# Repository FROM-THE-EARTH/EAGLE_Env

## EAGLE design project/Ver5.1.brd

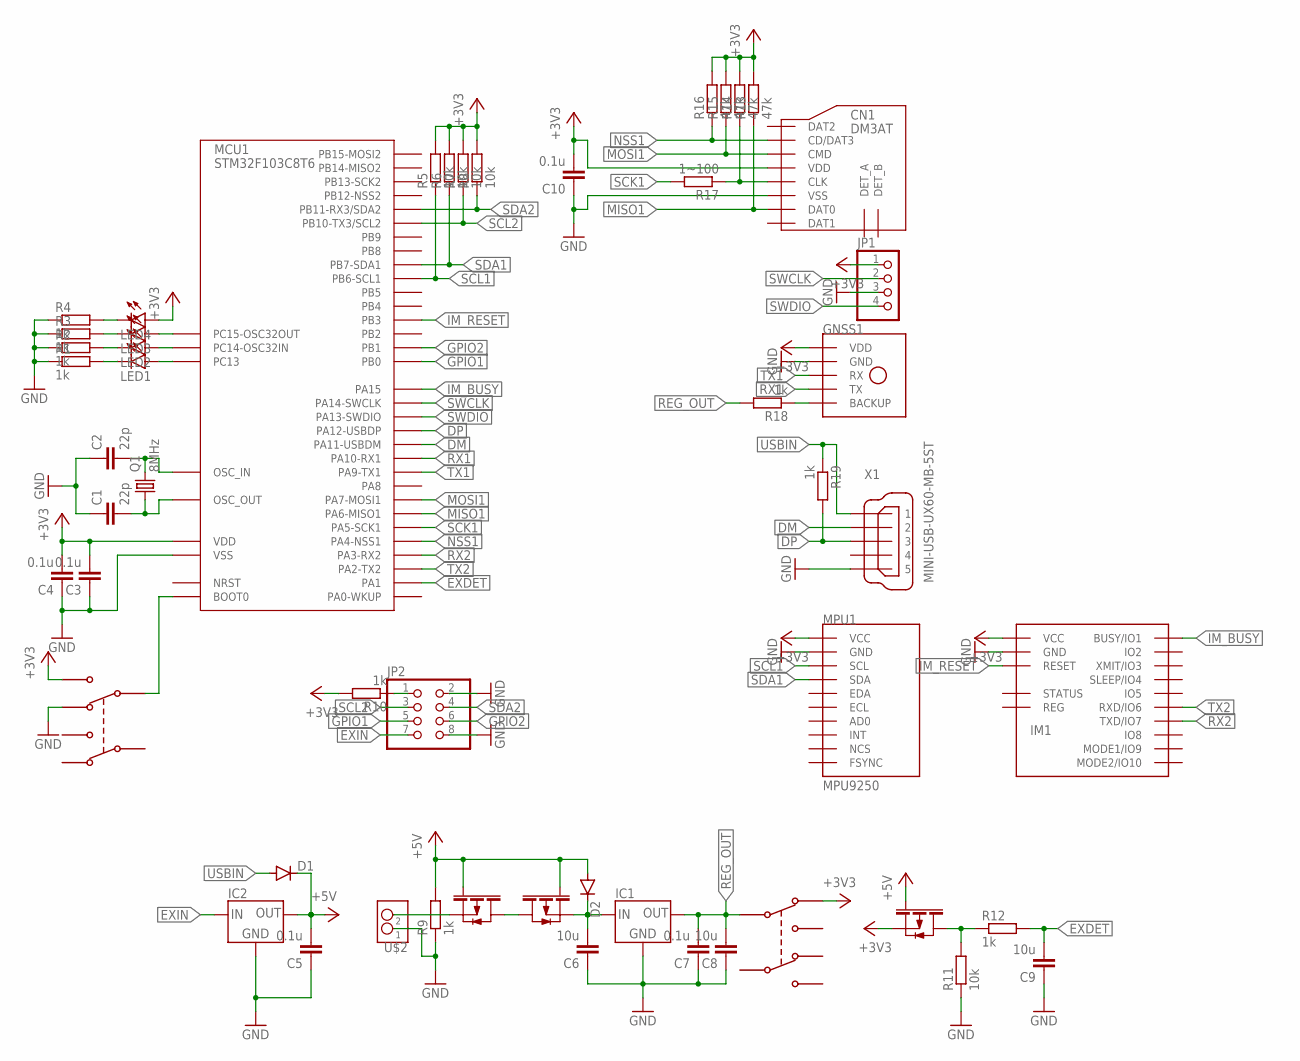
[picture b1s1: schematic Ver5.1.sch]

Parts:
C1, C2: 22p; C0805
C3, C4, C5, C7, C10: 0.1u; C0805
C6, C8, C9: 10u; C0805
CN1: DM3AT
D1, D2: DIODE-SOD123; SOD123
FET1, FET2, FET3: PCH; SOT-23
GNSS1: GYSFDMAXB
IC1: LT1117-3.3; SOT-223
IC2: LT1117-5; SOT-223
IM1: IM920C
JP1: PINHD-1X4/90; 1X04/90
JP2: PINHD-2X4; 2X04
LED1, LED2, LED3, LED4: LEDSML0805; SML0805
MCU1: STM32F103C8T6; LQFP48
MPU1: MPU9250; GY-9250
Q1: 8MHz; HC49/S
R1, R2, R3, R4, R9, R10, R12, R18, R19: 1k; R0805
R5, R6, R7, R8, R11: 10k; R0805
R13, R14, R15, R16: 47k; R0805
R17: 1~100; R0805
U$1, U$3: MSS22D18
U$2: S2B-XH-A
X1: MINI-USB-UX60-MB-5ST; UX60-MB-5ST

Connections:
+3V3: C3.2, C4.2, C10.2, CN1.VDD, FET3.P$2, GNSS1.P$16 (VDD), IM1.$P17 (VCC), JP1.1, LED4.A, MCU1.1 (VDD), MCU1.9 (VDD), MCU1.24 (VDD), MCU1.36 (VDD), MCU1.48 (VDD), MPU1.P1 (VCC), R5.2, R6.2, R7.2, R8.2, R10.2, R13.2, R14.2, R15.2, R16.2, U$1.P$0, U$3.P$3
+5V: C5.2, D1.C, D2.A, FET1.P$1, FET2.P$1, FET3.P$1, IC2.2 (OUT), R9.2
BOOT0: MCU1.44 (BOOT0), U$1.P$1
CLK_R: CN1.CLK, R14.1, R17.1
DM: MCU1.32 (PA11-USBDM), X1.2
DP: MCU1.33 (PA12-USBDP), R19.2, X1.3
EXDET: C9.2, MCU1.11 (PA1), R12.2
EXDET_R: FET3.P$3, R11.2, R12.1
EXIN: IC2.3 (IN), JP2.7
FET_FET: FET1.P$3, FET2.P$3
GND: C1.1, C2.1, C3.1, C4.1, C5.1, C6.1, C7.1, C8.1, C9.1, C10.1, CN1.VSS, GNSS1.P$1 (GND), GNSS1.P$2 (GND), GNSS1.P$7 (GND), GNSS1.P$10 (GND), GNSS1.P$12 (GND), GNSS1.P$19 (GND), GNSS1.P$20 (GND), IC1.4 (GND), IC2.4 (GND), IM1.$P18 (GND), JP1.3, JP2.2, JP2.8, MCU1.8 (VSS), MCU1.23 (VSS), MCU1.35 (VSS), MCU1.47 (VSS), MPU1.P2 (GND), R1.1, R2.1, R3.1, R4.1, R9.1, R11.1, U$1.P$2, U$2.P$1 (1), X1.5
GPIO1: JP2.5, MCU1.18 (PB0)
GPIO2: JP2.6, MCU1.19 (PB1)
GPS_BACKUP: GNSS1.P$14 (BACKUP), R18.1
IM_BUSY: IM1.$P1 (BUSY/IO1), MCU1.38 (PA15)
IM_RESET: IM1.$P19 (RESET), MCU1.39 (PB3)
LED1_R: LED1.C, R1.2
LED2_R: LED2.C, R2.2
LED3_R: LED3.C, R3.2
LED4_R: LED4.C, R4.2
LI_IN: FET1.P$2, U$2.P$2 (2)
MISO1: CN1.DAT0, MCU1.16 (PA6-MISO1), R13.1
MOSI1: CN1.CMD, MCU1.17 (PA7-MOSI1), R15.1
NSS1: CN1.CD/DAT3, MCU1.14 (PA4-NSS1), R16.1
OSC_IN: C2.2, MCU1.5 (OSC_IN), Q1.2
OSC_OUT: C1.2, MCU1.6 (OSC_OUT), Q1.1
PC13_LED: LED1.A, MCU1.2 (PC13)
PC14_LED: LED2.A, MCU1.3 (PC14-OSC32IN)
PC15_LED: LED3.A, MCU1.4 (PC15-OSC32OUT)
REG_IN: C6.2, D2.C, FET2.P$2, IC1.3 (IN)
REG_OUT: C7.2, C8.2, IC1.1 (OUT), IC1.2 (OUT), R18.2, U$3.P$4
RX1: GNSS1.P$5 (TX), MCU1.31 (PA10-RX1)
RX2: IM1.$P7 (TXD/IO7), MCU1.13 (PA3-RX2)
S3V3: JP2.1, R10.1
SCK1: MCU1.15 (PA5-SCK1), R17.2
SCL1: MCU1.42 (PB6-SCL1), MPU1.P3 (SCL), R5.1
SCL2: JP2.3, MCU1.21 (PB10-TX3/SCL2), R7.1
SDA1: MCU1.43 (PB7-SDA1), MPU1.P4 (SDA), R6.1
SDA2: JP2.4, MCU1.22 (PB11-RX3/SDA2), R8.1
SWCLK: JP1.2, MCU1.37 (PA14-SWCLK)
SWDIO: JP1.4, MCU1.34 (PA13-SWDIO)
TX1: GNSS1.P$3 (RX), MCU1.30 (PA9-TX1)
TX2: IM1.$P6 (RXD/IO6), MCU1.12 (PA2-TX2)
USBIN: D1.A, R19.1, X1.1

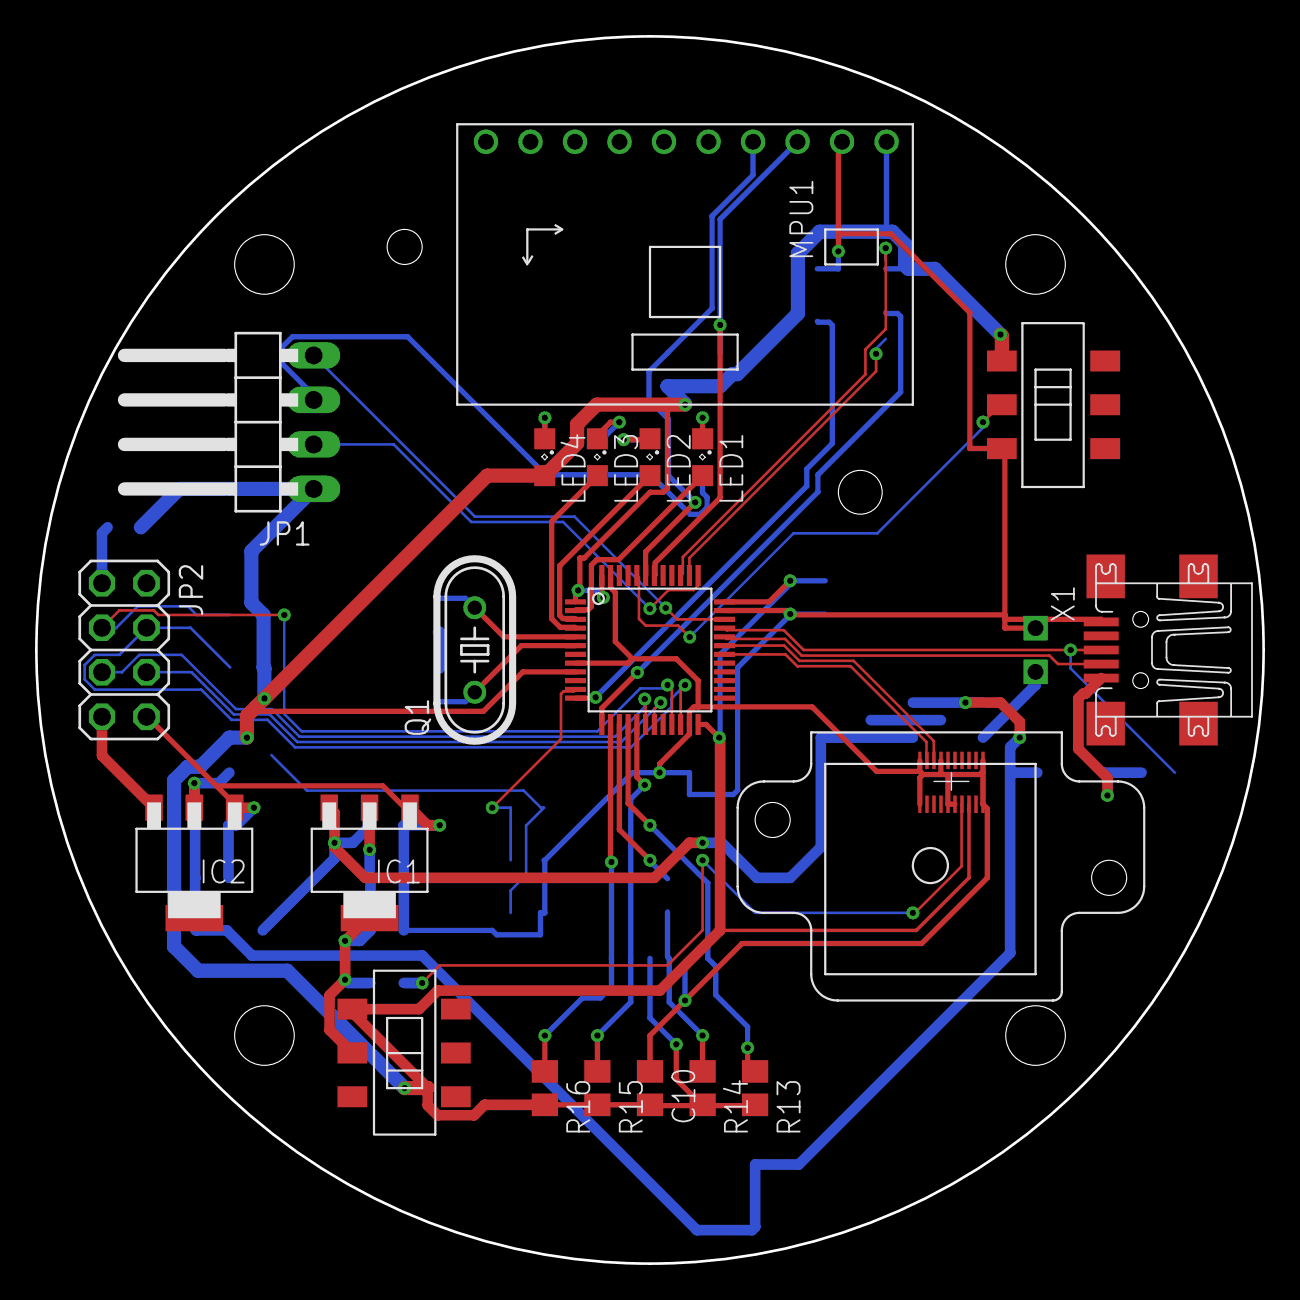
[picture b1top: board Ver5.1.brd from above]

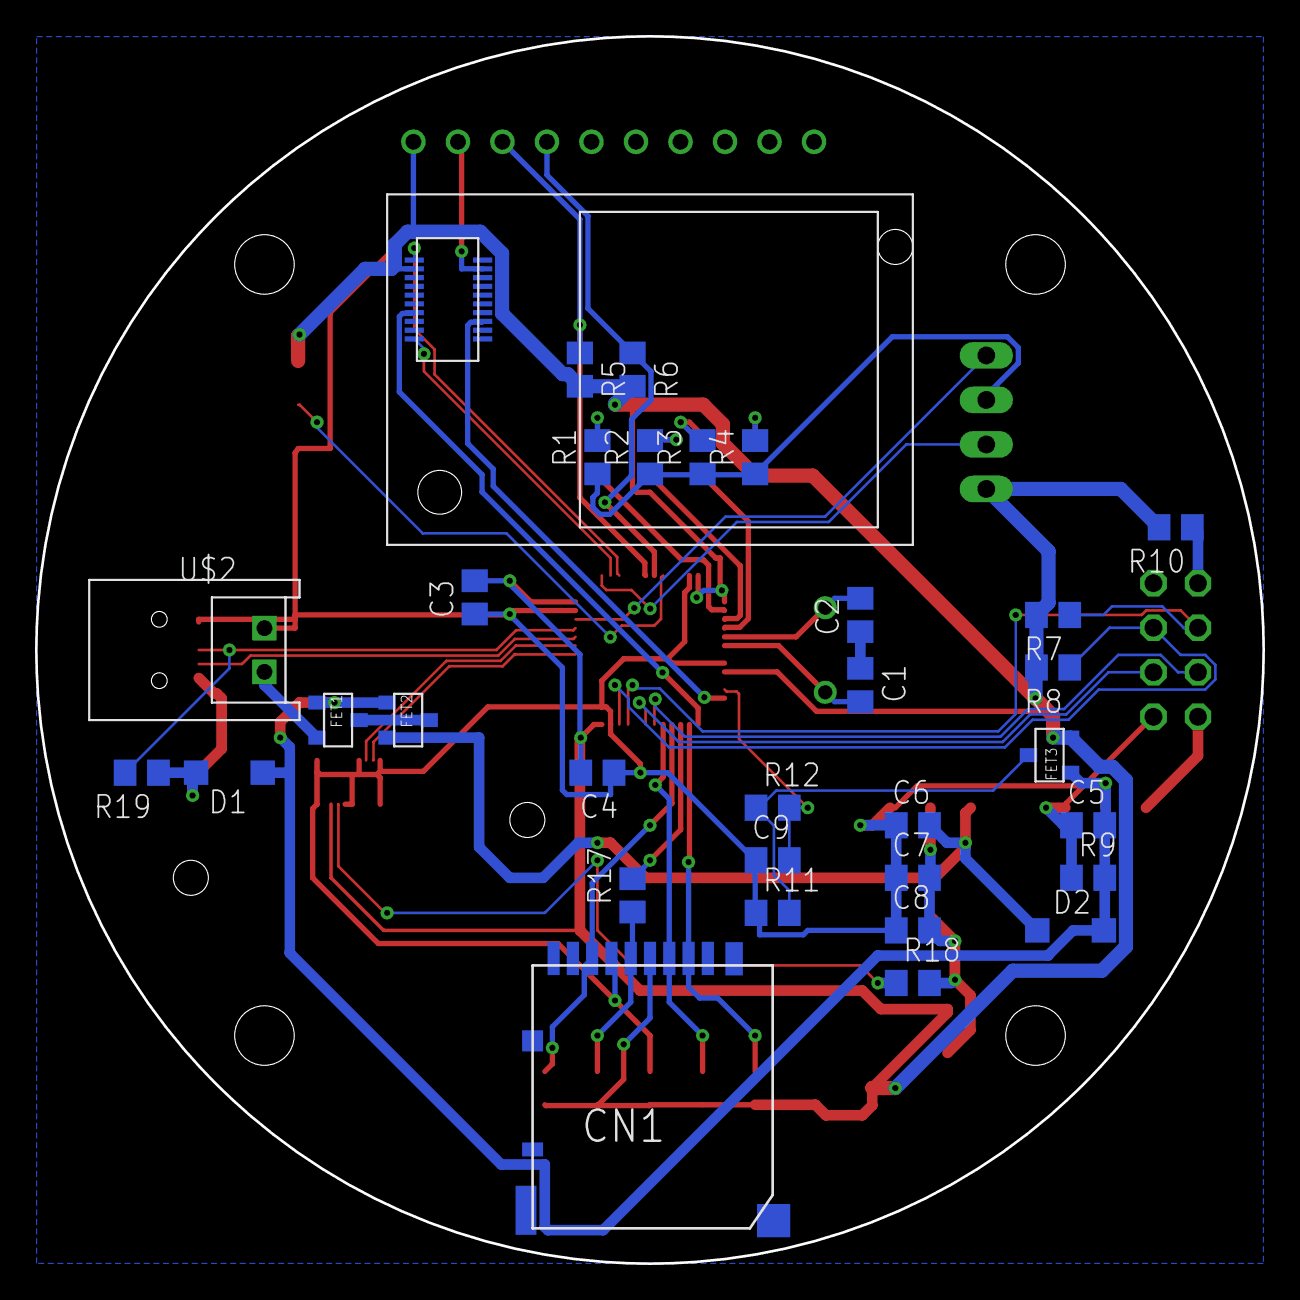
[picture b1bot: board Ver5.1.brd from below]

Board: 2 copper layers, 70.0 x 70.0 mm, 52 parts (32 on the bottom side), 44 nets.

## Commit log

2021-10-19 ライブラリと基板データ追加
2022-06-03 MOSFETのピン修正 いくつか追加
